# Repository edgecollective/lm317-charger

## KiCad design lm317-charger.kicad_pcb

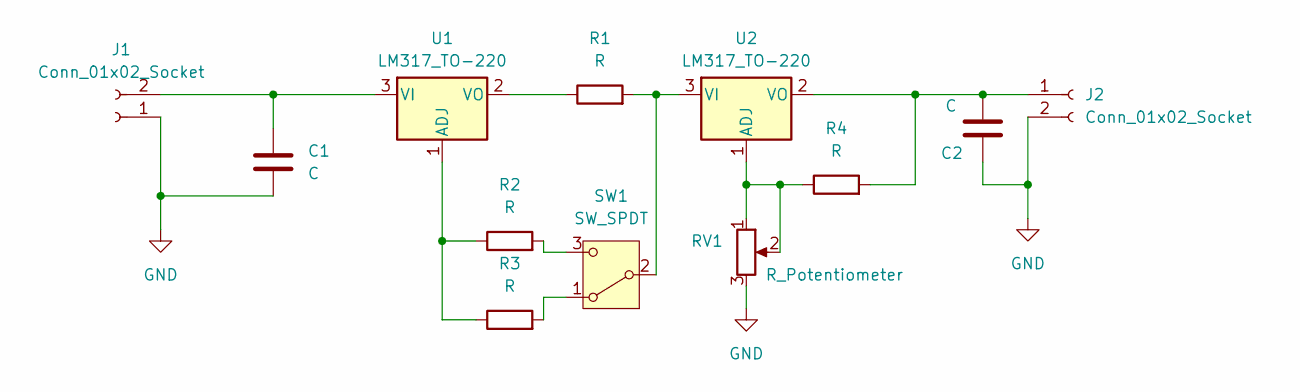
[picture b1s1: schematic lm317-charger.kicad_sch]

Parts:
C1, C2: C; C_Radial_D10.0mm_H12.5mm_P5.00mm
J1, J2: Conn_01x02_Socket; TerminalBlock_Phoenix_MKDS-1,5-2-5.08_1x02_P5.08mm_Horizont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
R1, R2, R3, R4: R; R_Axial_DIN0207_L6.3mm_D2.5mm_P10.16mm_Horizontal
RV1: R_Potentiometer; Potentiometer_Bourns_3386P_Vertical
SW1: SW_SPDT; usual_switch
U1, U2: LM317_TO-220; TO-220-3_Vertical

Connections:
GND: C1.2, C2.2, J1.1, J2.2, RV1.3
unnamed: C1.1, J1.2, U1.3 (VI)
unnamed: C2.1, J2.1, R4.2, U2.2 (VO)
unnamed: R3.2, SW1.1 (A)
unnamed: R1.2, SW1.2 (B), U2.3 (VI)
unnamed: R2.2, SW1.3 (C)
unnamed: R2.1, R3.1, U1.1 (ADJ)
unnamed: R1.1, U1.2 (VO)
unnamed: R4.1, RV1.1, RV1.2, U2.1 (ADJ)

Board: 2 copper layers, 12 parts (0 on the bottom side), 9 nets, no tracks yet.
